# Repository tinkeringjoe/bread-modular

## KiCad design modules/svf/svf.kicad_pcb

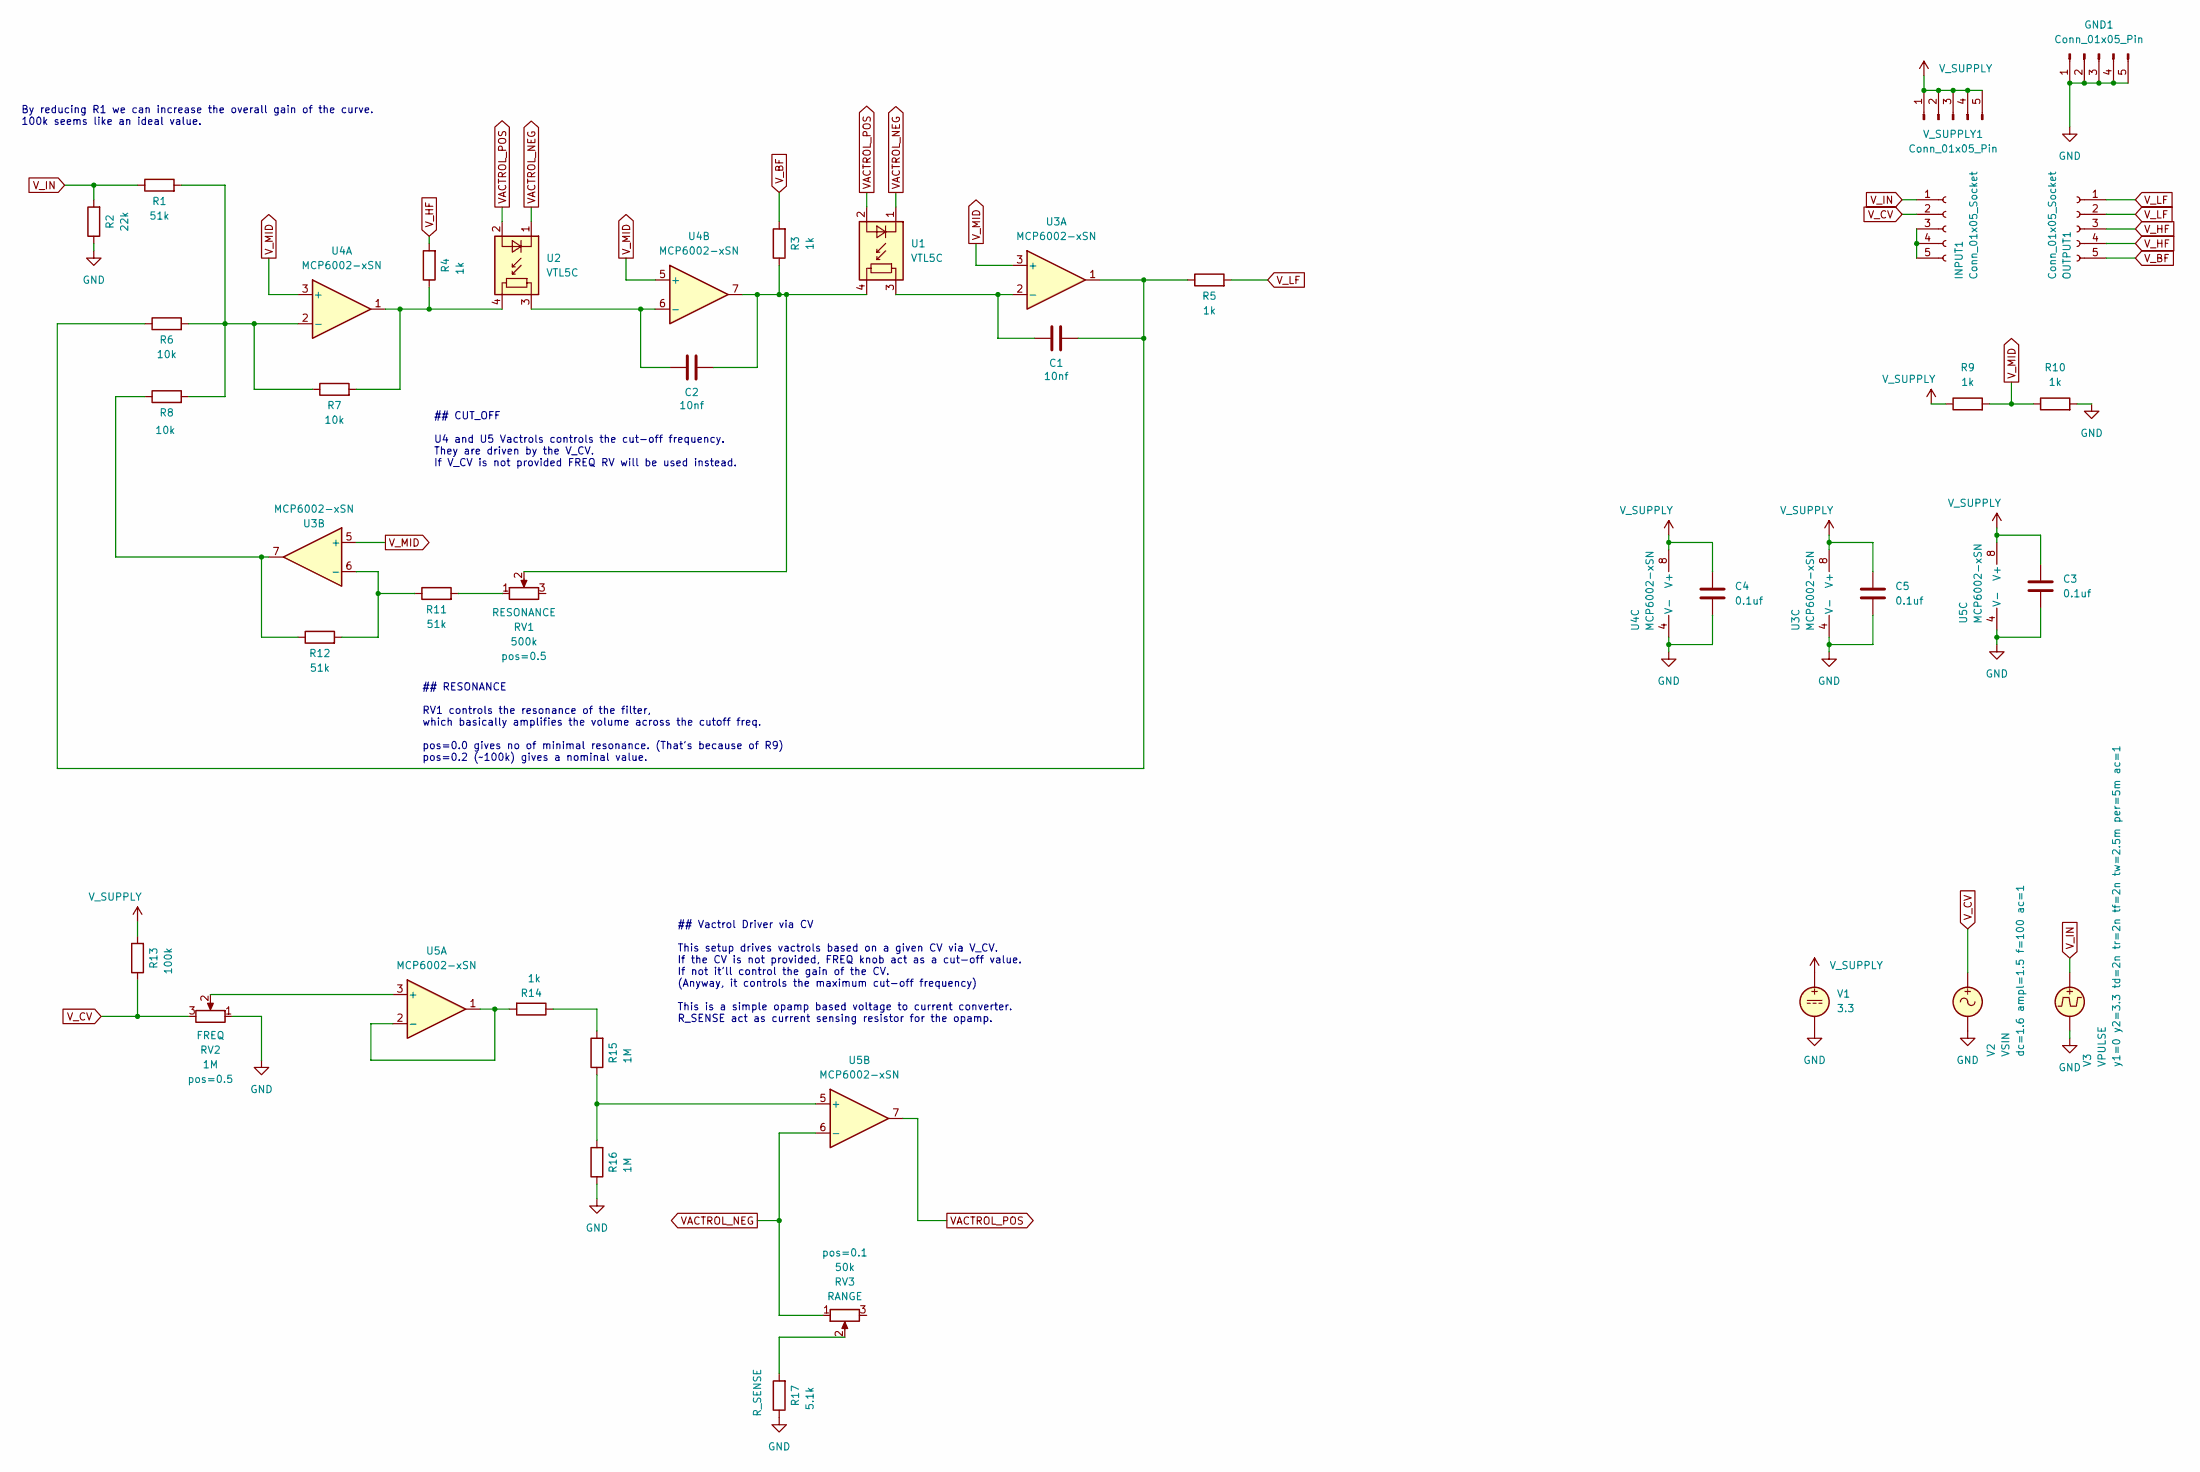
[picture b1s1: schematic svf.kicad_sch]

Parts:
C1, C2: 10nf; C_0402_1005Metric
C3, C4, C5: 0.1uf; C_0402_1005Metric
GND1: Conn_01x05_Pin; Power_Connector
INPUT1: Conn_01x05_Socket; PinSocket_1x05_P2.54mm_Vertical
OUTPUT1: Conn_01x05_Socket; PinSocket_1x05_P2.54mm_Vertical
R1, R11, R12: 51k; R_0402_1005Metric
R2: 22k; R_0402_1005Metric
R3, R4, R5, R9, R10, R14: 1k; R_0402_1005Metric
R6, R7, R8: 10k; R_0402_1005Metric
R13: 100k; R_0402_1005Metric
R15, R16: 1M; R_0402_1005Metric
R17: 5.1k; R_0402_1005Metric
RV1: 500k; Potentiometer_RV09
RV2: 1M; Potentiometer_RV09
RV3: 50k; Potentiometer_RV09
U1, U2: VTL5C
U3, U4, U5: MCP6002-xSN; SOIC-8-1EP_3.9x4.9mm_P1.27mm_EP2.29x3mm
V1: 3.3
V2: VSIN
V3: VPULSE
V_SUPPLY1: Conn_01x05_Pin; Power_Connector

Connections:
GND: C3.2, C4.2, C5.2, GND1.1, GND1.2, GND1.3, GND1.4, GND1.5, R2.1, R10.2, R16.1, R17.1, RV2.1, U3.4 (V-), U4.4 (V-), U5.4 (V-), V1.2, V2.2, V3.2
unnamed: C1.2, R5.1, R6.1, U3.1
unnamed: C2.2, R3.1, RV1.2, U1.4, U4.7
unnamed: INPUT1.3, INPUT1.4, INPUT1.5
unnamed: R4.1, R7.2, U2.4, U4.1
unnamed: R11.2, RV1.1
unnamed: R8.1, R12.1, U3.7
unnamed: R14.1, R15.2
unnamed: R17.2, RV3.2
unnamed: C1.1, U1.3, U3.2 (-)
unnamed: R11.1, R12.2, U3.6 (-)
unnamed: R1.2, R6.2, R7.1, R8.2, U4.2 (-)
unnamed: C2.1, U2.3, U4.6 (-)
unnamed: RV2.2, U5.3 (+)
unnamed: R14.2, U5.1, U5.2 (-)
unnamed: R15.1, R16.2, U5.5 (+)
VACTROL_NEG: RV3.1, U1.1 (-), U2.1 (-), U5.6 (-)
VACTROL_POS: U1.2 (+), U2.2 (+), U5.7
V_BF: OUTPUT1.5, R3.2
V_CV: INPUT1.2, R13.1, RV2.3, V2.1
V_HF: OUTPUT1.3, OUTPUT1.4, R4.2
V_IN: INPUT1.1, R1.1, R2.2, V3.1
V_LF: OUTPUT1.1, OUTPUT1.2, R5.2
V_MID: R9.2, R10.1, U3.3 (+), U3.5 (+), U4.3 (+), U4.5 (+)
V_SUPPLY: C3.1, C4.1, C5.1, R9.1, R13.2, U3.8 (V+), U4.8 (V+), U5.8 (V+), V1.1, V_SUPPLY1.1, V_SUPPLY1.2, V_SUPPLY1.3, V_SUPPLY1.4, V_SUPPLY1.5

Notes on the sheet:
## Vactrol Driver via CV This setup drives vactrols based on a given CV via V_CV. If the CV is not provided, FREQ knob act as a cut-off value. If not it'll control the gain of the CV. (Anyway, it controls the maximum cut-off frequency) This is a simple opamp based voltage to current converter. R_SE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
## CUT_OFF U4 and U5 Vactrols controls the cut-off frequency. They are driven by the V_CV. If V_CV is not provided FREQ RV will be used instead.
## RESONANCE RV1 controls the resonance of the filter, which basically amplifies the volume across the cutoff freq. pos=0.0 gives no of minimal resonance. (That's because of R9) pos=0.2 (~100k) gives a nominal value.
By reducing R1 we can increase the overall gain of the curve. 100k seems like an ideal value.

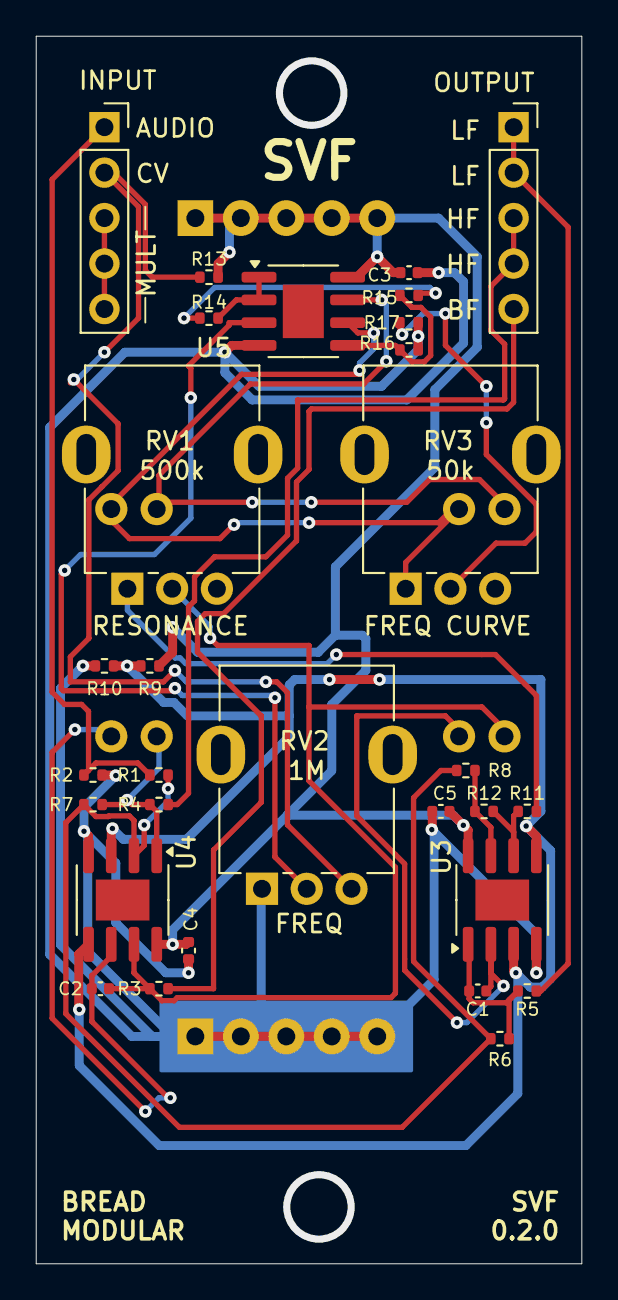
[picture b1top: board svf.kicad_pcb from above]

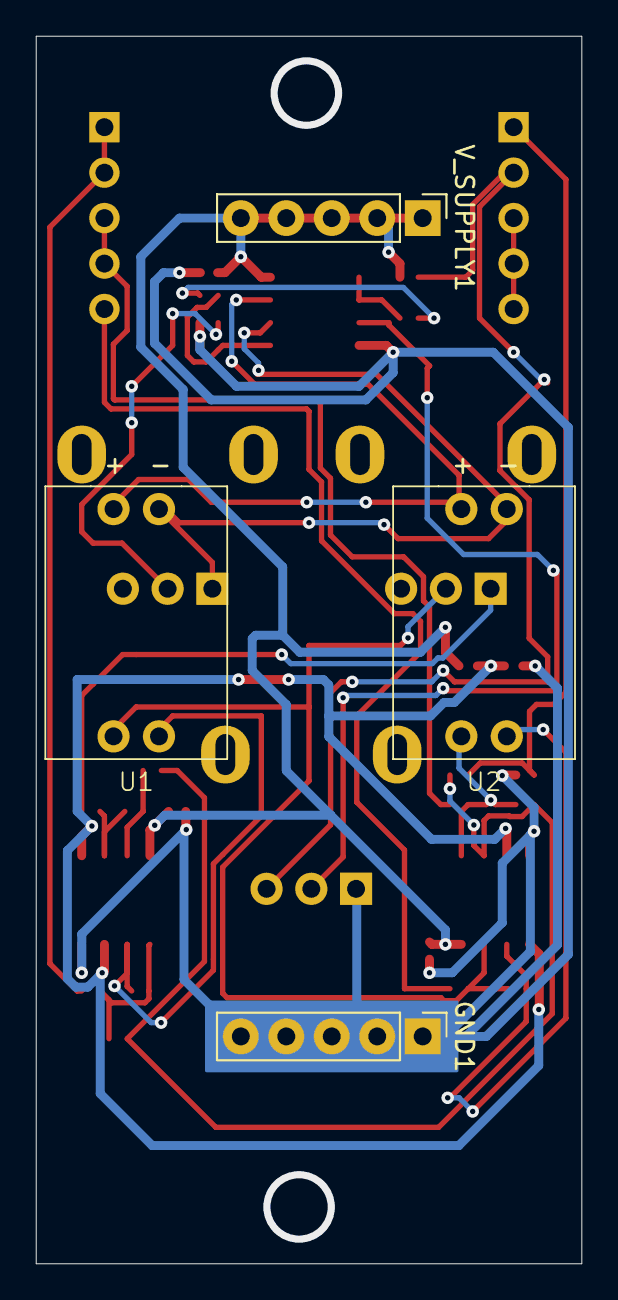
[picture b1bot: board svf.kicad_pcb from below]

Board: 2 copper layers, 30.5 x 68.6 mm, 34 parts (4 on the bottom side), 25 nets.

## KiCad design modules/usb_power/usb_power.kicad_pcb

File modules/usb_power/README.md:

# USB_Power

A simple power source from USB.

## Usage

This plug a USB-C and now we have power to the system.<br/>
This makes is not only to get power from computer, but using bunch of power source including your phone. This will be the only power source we'll ever need.

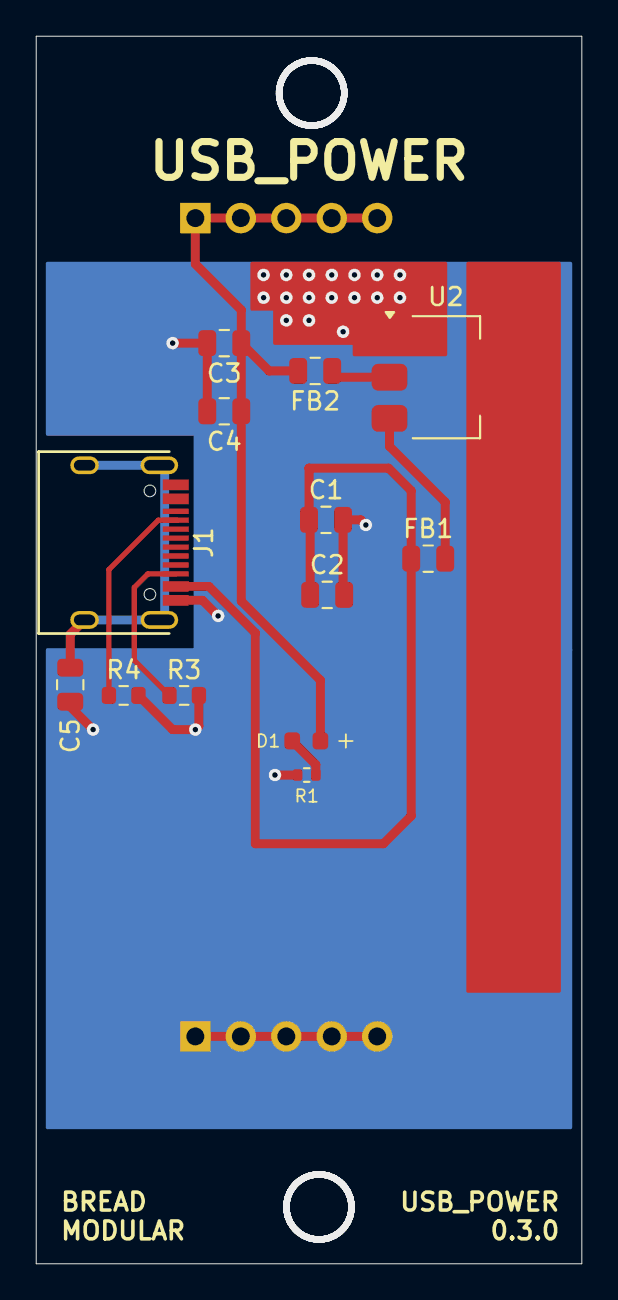
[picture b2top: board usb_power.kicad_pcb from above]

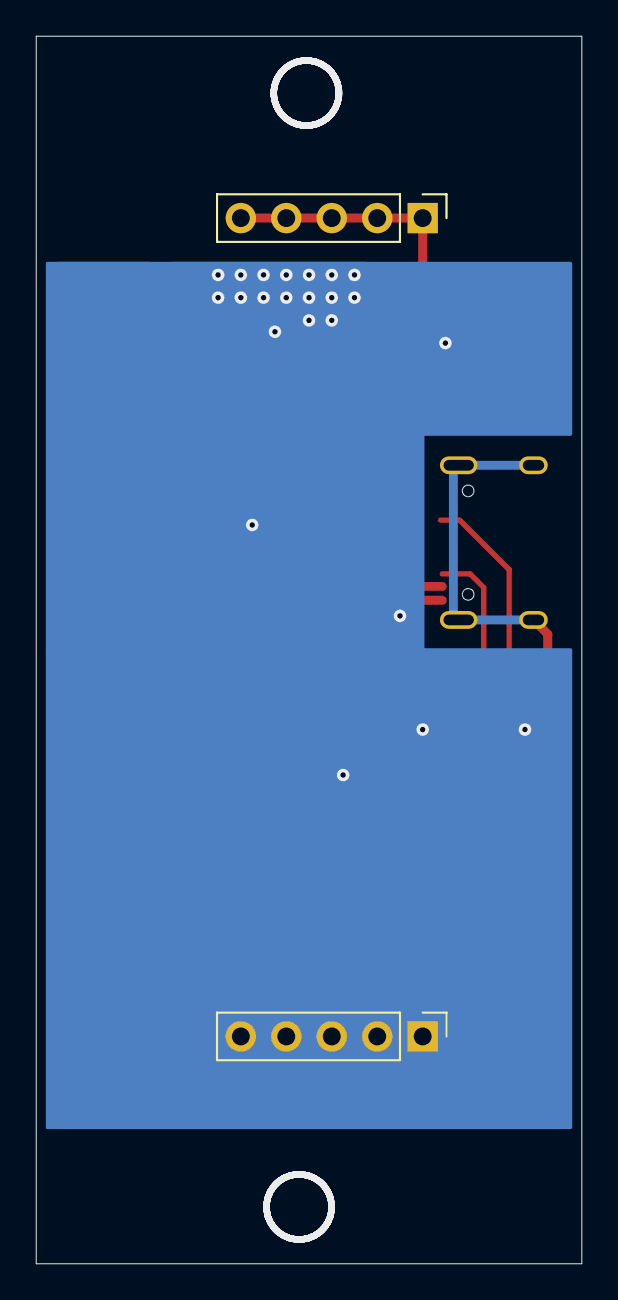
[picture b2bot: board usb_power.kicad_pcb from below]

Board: 2 copper layers, 30.5 x 68.6 mm, 15 parts (2 on the bottom side), 9 nets.

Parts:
5V1: Conn_01x05_Pin; PinHeader_1x05_P2.54mm_Vertical
C1, C3: 10uf; C_0805_2012Metric
C2, C4: 0.1uf; C_0805_2012Metric
C5: 10nf; C_0805_2012Metric
D1: LED; LED_0603_1608Metric
FB1, FB2: GZ2012E800TF; C_0805_2012Metric
GND1: Conn_01x05_Pin; PinHeader_1x05_P2.54mm_Vertical
J1: USB_C_Receptacle_PowerOnly_6P; HRO-TYPE-C-31-M-12
R1: 1k; R_0402_1005Metric
R3, R4: 5.1k; R_0603_1608Metric
U2: AMS1117-3.3; SOT-223

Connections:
+3.3V: 5V1.1, 5V1.2, 5V1.3, 5V1.4, 5V1.5, C3.1, C4.1, D1.2 (A), FB2.2
GND: C1.2, C2.2, C3.2, C4.2, C5.2, GND1.1, GND1.2, GND1.3, GND1.4, GND1.5, J1.A12 (GND), R1.2, R3.2, R4.2, U2.1 (GND)
unnamed: C1.1, C2.1, FB1.1, J1.A9 (VBUS)
unnamed: D1.1 (K), R1.1
unnamed: J1.A5 (CC1), R4.1
unnamed: J1.B5 (CC2), R3.1
unnamed: C5.1, J1.S1 (SHIELD)
unnamed: FB1.2, U2.3 (VI)
unnamed: FB2.1, U2.2 (VO)

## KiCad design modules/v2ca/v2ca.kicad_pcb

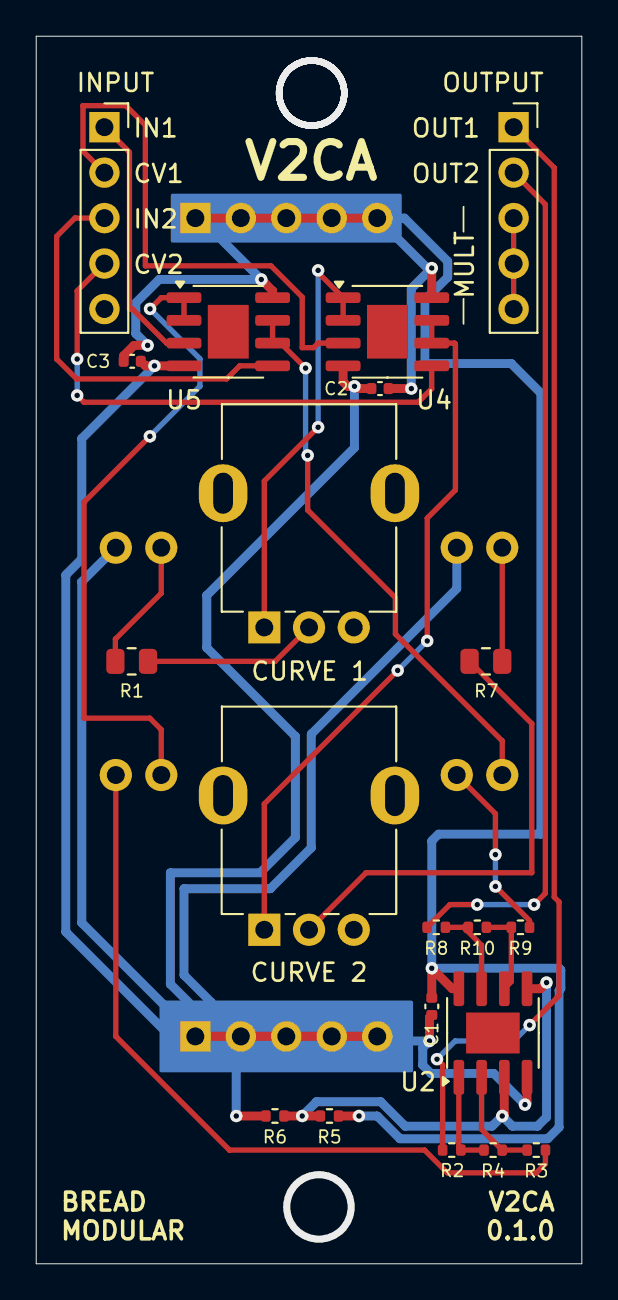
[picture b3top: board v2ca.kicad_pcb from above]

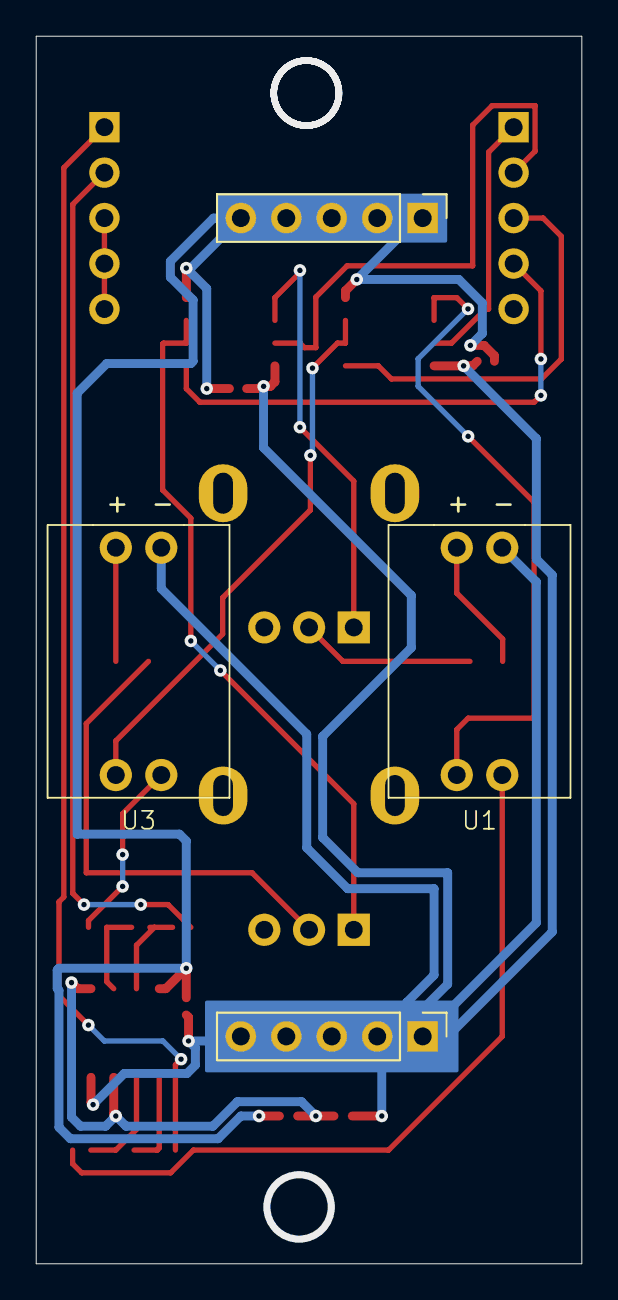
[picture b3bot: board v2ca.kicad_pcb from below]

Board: 2 copper layers, 30.5 x 68.6 mm, 24 parts (4 on the bottom side), 24 nets.

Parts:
5V1: Conn_01x05_Pin; PinHeader_1x05_P2.54mm_Vertical
C1, C2, C3: 0.1uf; C_0402_1005Metric
GND1: Conn_01x05_Pin; PinHeader_1x05_P2.54mm_Vertical
INPUT1: Conn_01x05_Socket; PinSocket_1x05_P2.54mm_Vertical
OUTPUT1: Conn_01x05_Socket; PinSocket_1x05_P2.54mm_Vertical
R1, R7: 330; R_0805_2012Metric
R2, R5, R6, R8: 1k; R_0402_1005Metric
R3, R4, R9, R10: 10k; R_0402_1005Metric
RV1, RV2: 50k; Potentiometer_RV09
U1, U3: VTL5C
U2, U4, U5: MCP6002-xSN; SOIC-8-1EP_3.9x4.9mm_P1.27mm_EP2.29x3mm

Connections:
+2.5V: R5.2, R6.1, U2.3 (+), U2.5 (+)
+5V: 5V1.1, 5V1.2, 5V1.3, 5V1.4, 5V1.5, C1.1, C2.1, C3.1, R5.1, U2.8 (V+), U4.8 (V+), U5.8 (V+)
CV1_IN: INPUT1.2, U4.3 (+)
CV2_IN: INPUT1.4, U4.5 (+)
GND: C1.2, C2.2, C3.2, GND1.1, GND1.2, GND1.3, GND1.4, GND1.5, R6.2, U1.1 (-), U2.4 (V-), U3.1 (-), U4.4 (V-), U5.4 (V-)
unnamed: OUTPUT1.3, OUTPUT1.4, OUTPUT1.5
unnamed: R1.1, RV1.2
unnamed: R2.1, R4.2, U2.1
unnamed: R3.1, U1.3
unnamed: R7.1, RV2.2
unnamed: R9.1, U3.3
unnamed: R8.1, R10.2, U2.7
unnamed: R1.2, U1.2 (+)
unnamed: R3.2, R4.1, U2.2 (-)
unnamed: R9.2, R10.1, U2.6 (-)
unnamed: R7.2, U3.2 (+)
unnamed: RV1.1, U4.1, U4.2 (-)
unnamed: RV2.1, U4.6 (-), U4.7
unnamed: U1.4, U5.1, U5.2 (-)
unnamed: U3.4, U5.6 (-), U5.7
V1_IN: INPUT1.1, U5.3 (+)
V1_OUT: OUTPUT1.1, R2.2
V2_IN: INPUT1.3, U5.5 (+)
V2_OUT: OUTPUT1.2, R8.2

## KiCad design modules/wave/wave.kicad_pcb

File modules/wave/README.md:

# Wave

A Simple Waveform generator based on opamp relaxation oscillators. It can generate:

* Square
* Triangle 
* Sine (only upword 45Hz)

## Configurations

Before we use this module, we need to configure and select the frequence range via the config jumping panel.

Here are the frequency ranges:

* LFO - 0.22Hz to 22Hz
* LOW - 15Hz to 1.5kHz
* HIGH - 227Hz to 22kHz
* C1 & C2 - Add custom capacitors
  (Resistance => Min: 10k, Max: 1M)

## Usage

You can select the frequency using "FREQ" potentiometer which is 1M ohms. Then you can fine tune it via the 50k ohms "FINE" potentiometer.

(Turning clockwise reduces the resistance)

## Notes

* Does not produce any results, when it's not configured
* Triangle waveform is appoximated & it's not a pure triangle
* Sine wave got distroted when the frequncy is below 45Hz
* Sine wave will be attenuated as the freq increases
* No voltage control input or modulation is supported

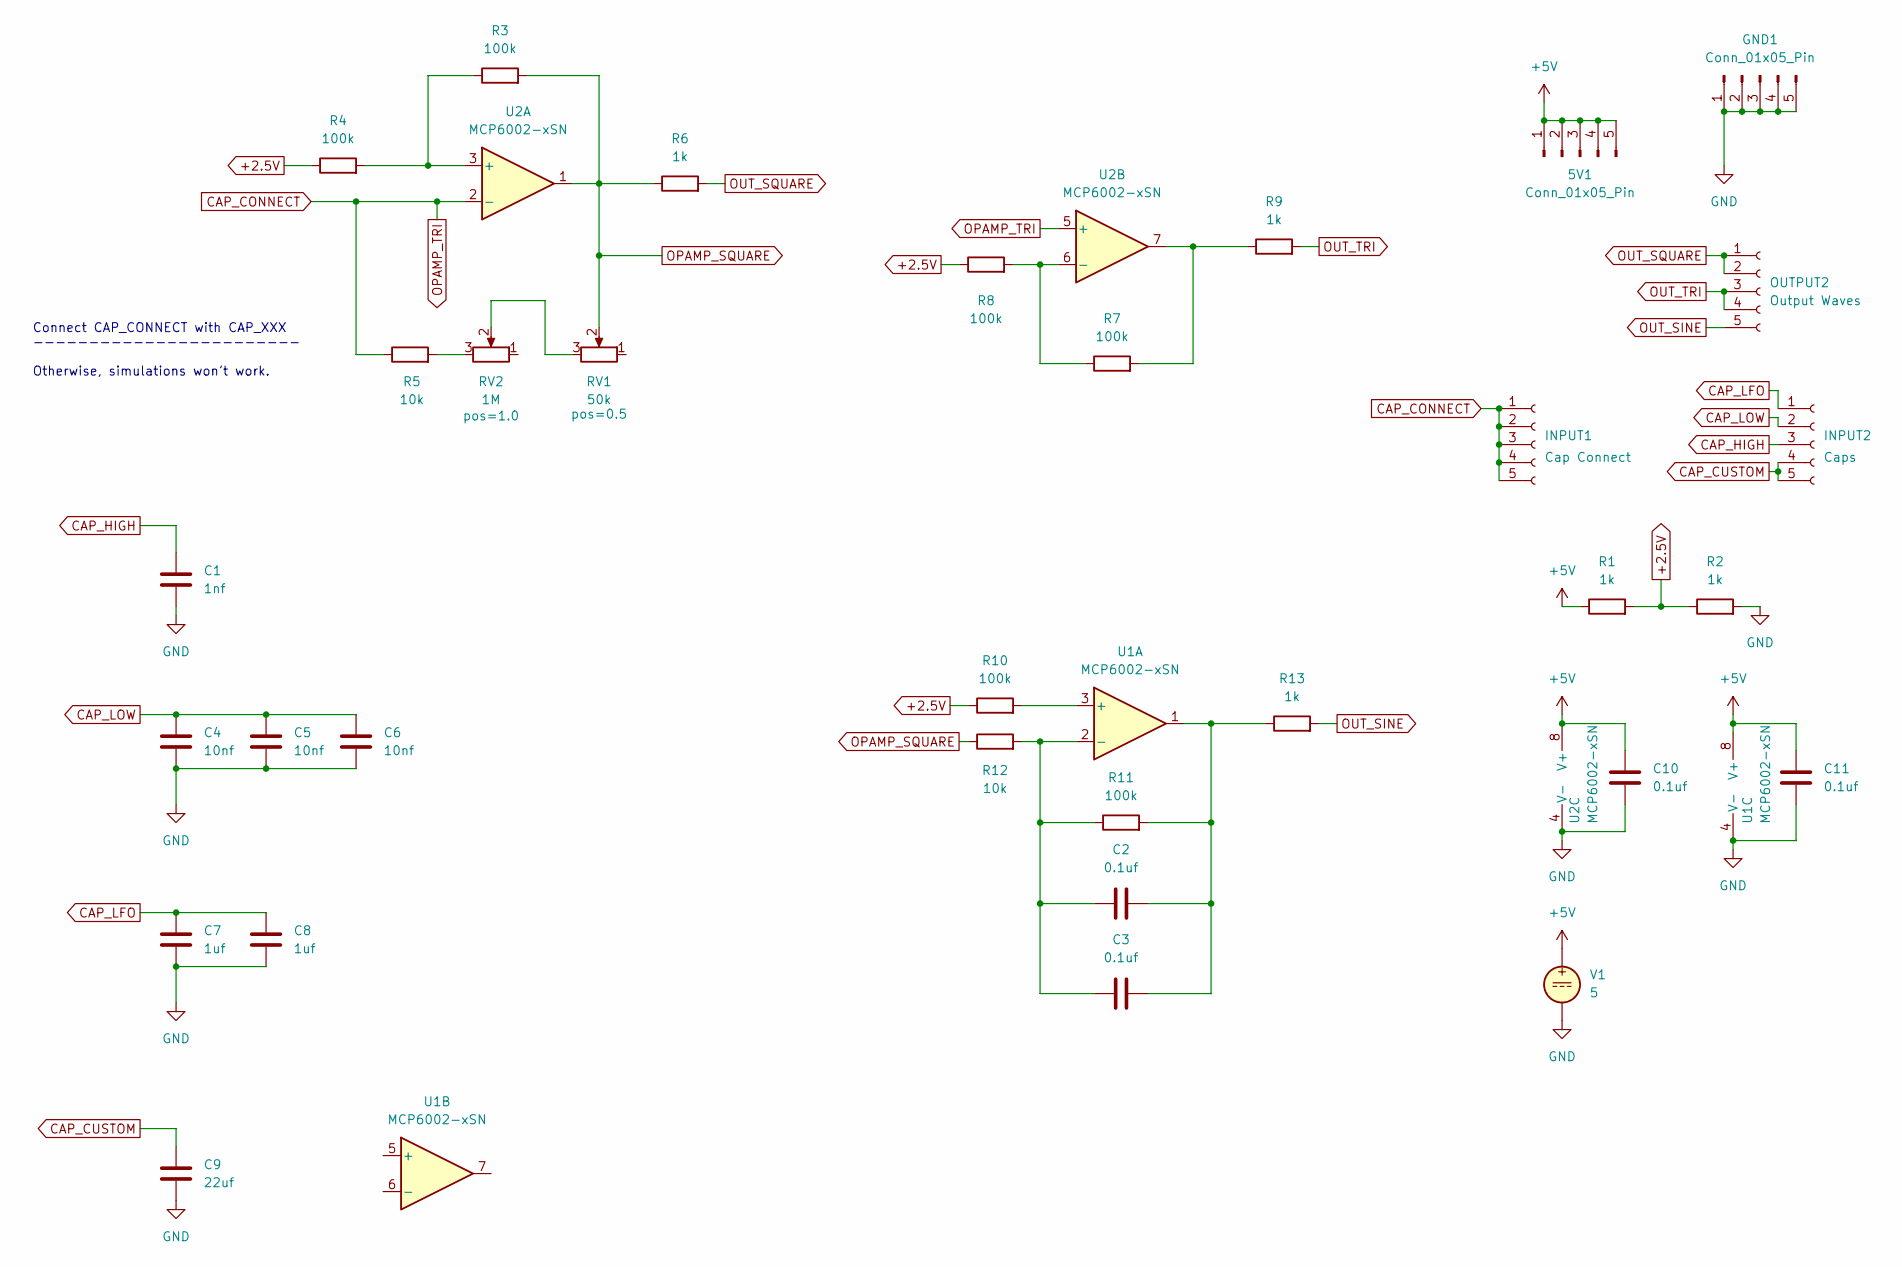
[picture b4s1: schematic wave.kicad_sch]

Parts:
5V1: Conn_01x05_Pin; PinHeader_1x05_P2.54mm_Vertical
C1: 1nf; C_0402_1005Metric
C2, C3, C10, C11: 0.1uf; C_0402_1005Metric
C4, C5, C6: 10nf; C_0402_1005Metric
C7, C8: 1uf; C_0402_1005Metric
C9: 22uf; C_0805_2012Metric
GND1: Conn_01x05_Pin; PinHeader_1x05_P2.54mm_Vertical
INPUT1: Cap Connect; PinSocket_1x05_P2.54mm_Vertical
INPUT2: Caps; PinSocket_1x05_P2.54mm_Vertical
OUTPUT2: Output Waves; PinSocket_1x05_P2.54mm_Vertical
R1, R2, R6, R9, R13: 1k; R_0402_1005Metric
R3, R4, R7, R8, R10, R11: 100k; R_0402_1005Metric
R5, R12: 10k; R_0402_1005Metric
RV1: 50k; Potentiometer_RV09
RV2: 1M; Potentiometer_RV09
U1, U2: MCP6002-xSN; SOIC-8-1EP_3.9x4.9mm_P1.27mm_EP2.29x3mm
V1: 5

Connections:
+2.5V: R1.2, R2.1, R4.1, R8.1, R10.1
+5V: 5V1.1, 5V1.2, 5V1.3, 5V1.4, 5V1.5, C10.1, C11.1, R1.1, U1.8 (V+), U2.8 (V+), V1.1
CAP_CONNECT: INPUT1.1, INPUT1.2, INPUT1.3, INPUT1.4, INPUT1.5, R5.1, U2.2 (-), U2.5 (+)
CAP_CUSTOM: C9.1, INPUT2.4, INPUT2.5
CAP_HIGH: C1.1, INPUT2.3
CAP_LFO: C7.1, C8.1, INPUT2.1
CAP_LOW: C4.1, C5.1, C6.1, INPUT2.2
GND: C1.2, C4.2, C5.2, C6.2, C7.2, C8.2, C9.2, C10.2, C11.2, GND1.1, GND1.2, GND1.3, GND1.4, GND1.5, R2.2, U1.4 (V-), U2.4 (V-), V1.2
unnamed: C2.2, C3.2, R11.2, R13.1, U1.1
unnamed: R5.2, RV2.3
unnamed: R7.2, R9.1, U2.7
unnamed: RV1.3, RV2.2
unnamed: R10.2, U1.3 (+)
unnamed: C2.1, C3.1, R11.1, R12.2, U1.2 (-)
unnamed: R3.1, R4.2, U2.3 (+)
unnamed: R7.1, R8.2, U2.6 (-)
OPAMP_SQUARE: R3.2, R6.1, R12.1, RV1.2, U2.1
OUT_SINE: OUTPUT2.5, R13.2
OUT_SQUARE: OUTPUT2.1, OUTPUT2.2, R6.2
OUT_TRI: OUTPUT2.3, OUTPUT2.4, R9.2

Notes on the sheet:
Connect CAP_CONNECT with CAP_XXX ------------------------ Otherwise, simulations won't work.

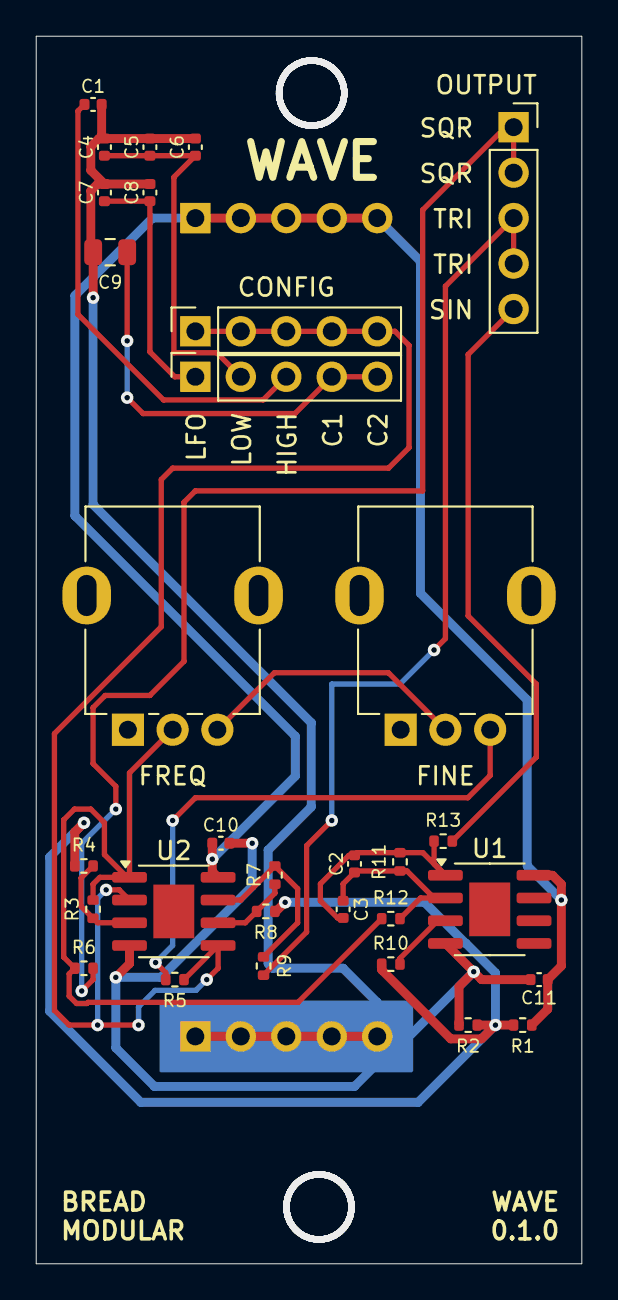
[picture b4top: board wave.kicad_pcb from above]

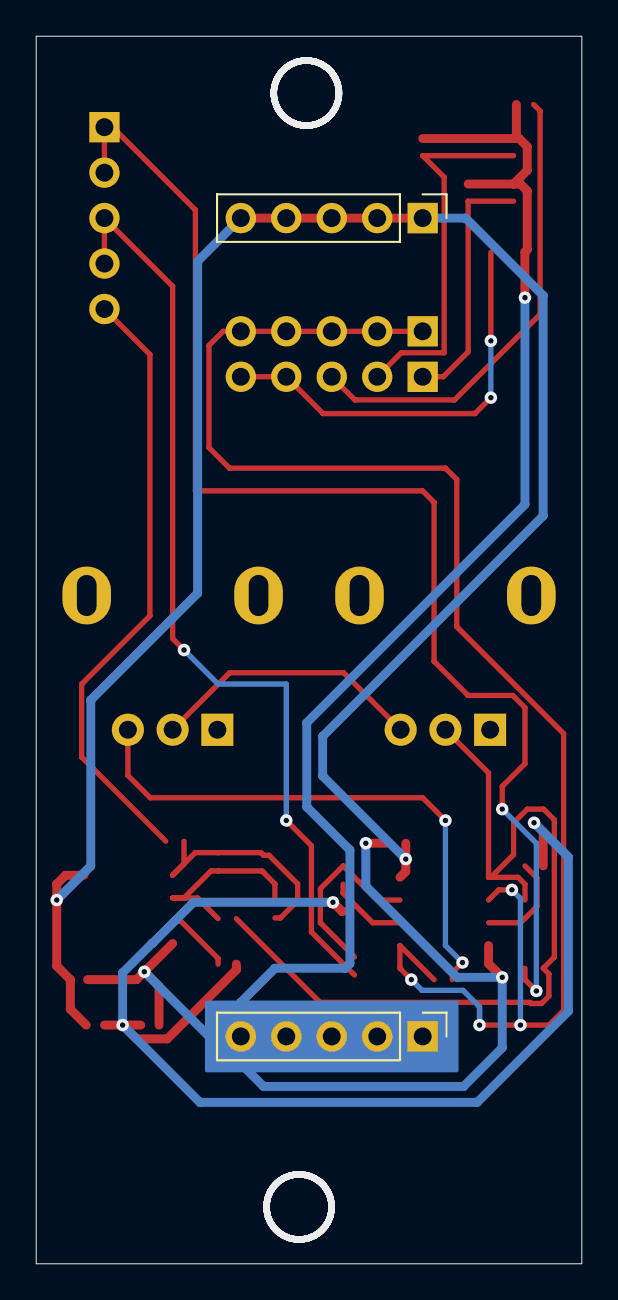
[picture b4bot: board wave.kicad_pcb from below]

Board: 2 copper layers, 30.5 x 68.6 mm, 33 parts (2 on the bottom side), 20 nets.

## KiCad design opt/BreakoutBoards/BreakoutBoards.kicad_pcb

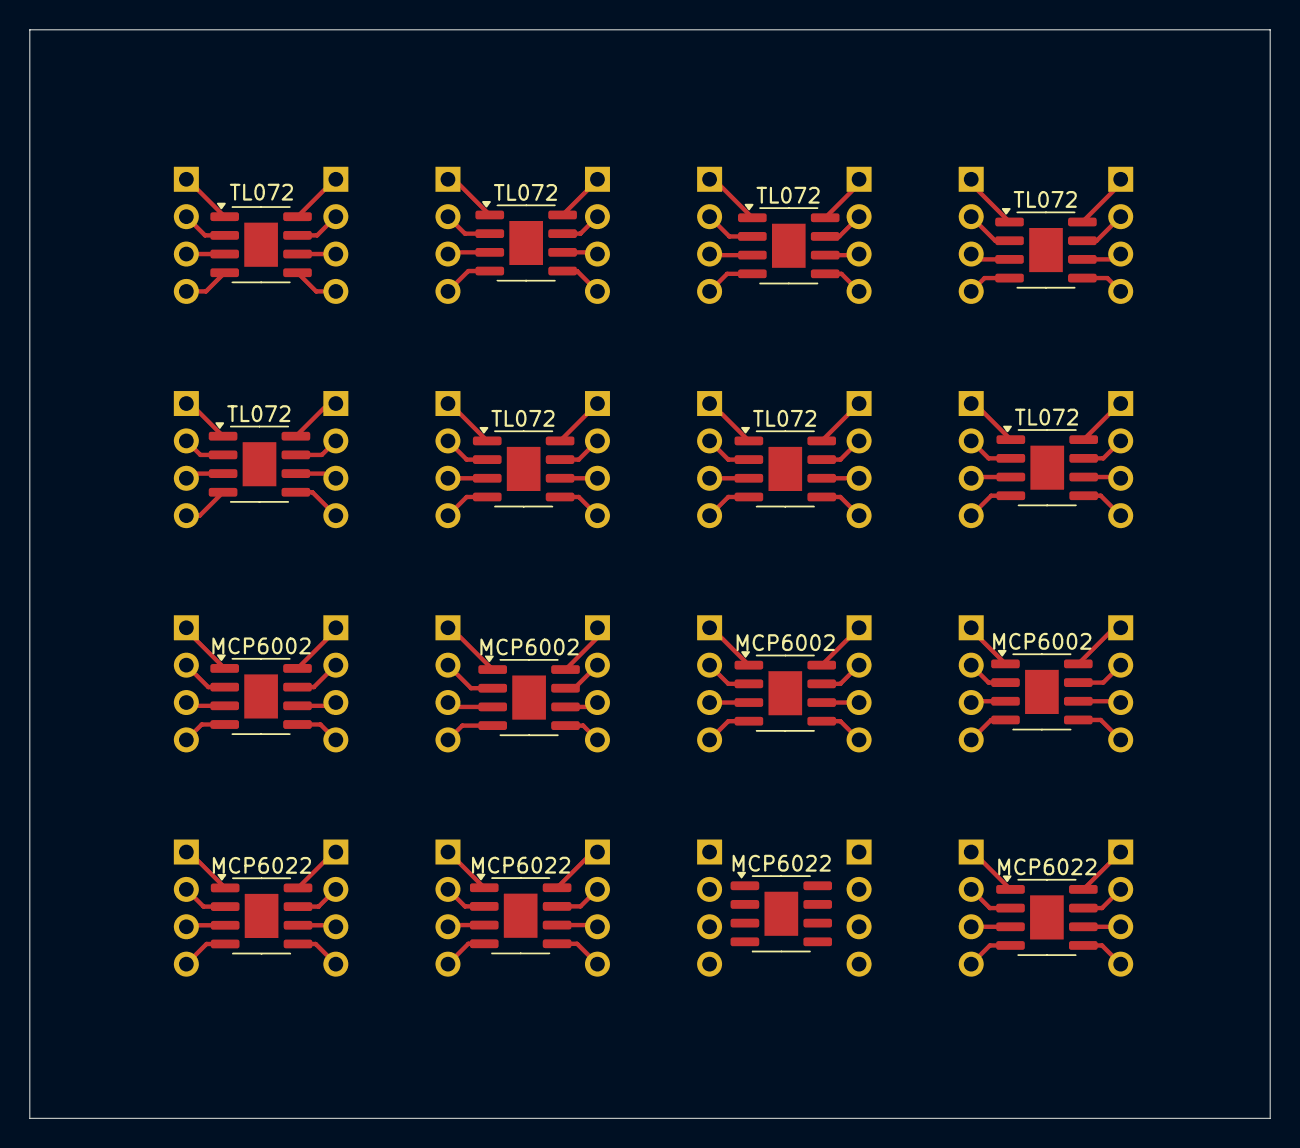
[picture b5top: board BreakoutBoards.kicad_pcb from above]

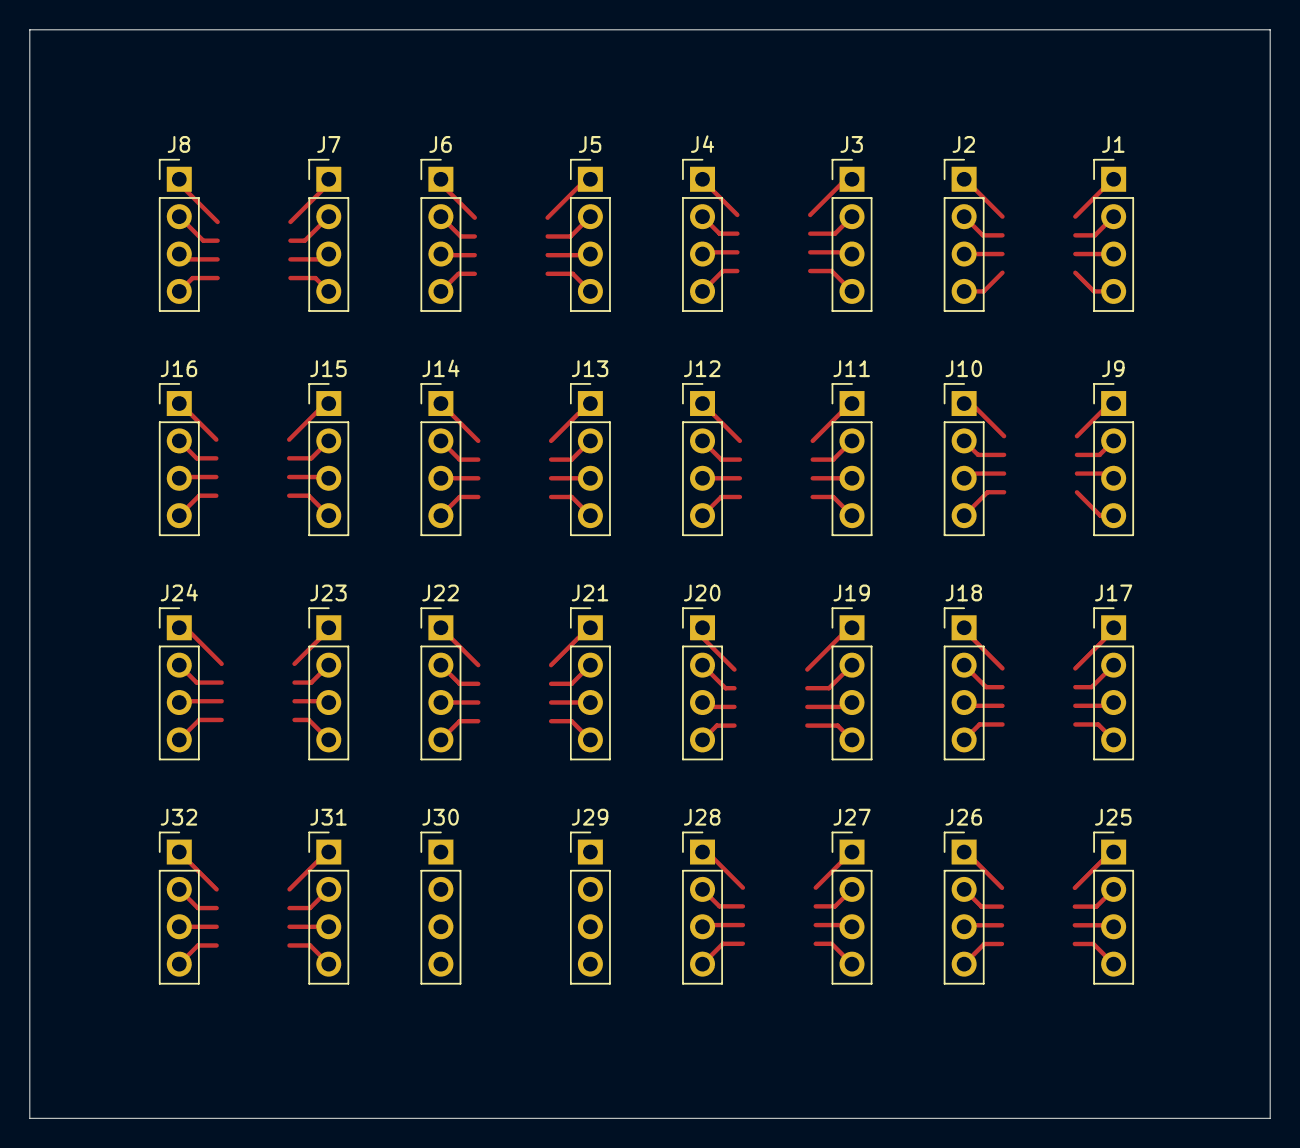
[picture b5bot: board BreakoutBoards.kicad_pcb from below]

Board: 2 copper layers, 84.3 x 74.0 mm, 48 parts (32 on the bottom side), 128 nets.

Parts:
J1, J2, J3, J4, J5, J6, J7, J8, J9, J10, J11, J12, J13, J14, J15, J16, J17, J18, J19, J20, J21, J22, J23, J24, J25, J26, J27, J28, J29, J30, J31, J32: Conn_01x04_Pin; PinHeader_1x04_P2.54mm_Vertical
MCP6002, MCP6002#2, MCP6002#3, MCP6002#4: MCP6002-xSN; SOIC-8-1EP_3.9x4.9mm_P1.27mm_EP2.29x3mm
MCP6022, MCP6022#2, MCP6022#3, MCP6022#4: MCP6022; SOIC-8-1EP_3.9x4.9mm_P1.27mm_EP2.29x3mm
TL072, TL072#2, TL072#3, TL072#4, TL072#5, TL072#6, TL072#7, TL072#8: TL072; SOIC-8-1EP_3.9x4.9mm_P1.27mm_EP2.29x3mm

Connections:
unnamed: J1.1, TL072.1
unnamed: J1.2, TL072.2 (-)
unnamed: J1.3, TL072.3 (+)
unnamed: J1.4, TL072.4 (V-)
unnamed: J2.1, TL072.8 (V+)
unnamed: J2.2, TL072.7
unnamed: J2.3, TL072.6 (-)
unnamed: J2.4, TL072.5 (+)
unnamed: J3.1, TL072#2.1
unnamed: J3.2, TL072#2.2 (-)
unnamed: J3.3, TL072#2.3 (+)
unnamed: J3.4, TL072#2.4 (V-)
unnamed: J4.1, TL072#2.8 (V+)
unnamed: J4.2, TL072#2.7
unnamed: J4.3, TL072#2.6 (-)
unnamed: J4.4, TL072#2.5 (+)
unnamed: J5.1, TL072#6.1
unnamed: J5.2, TL072#6.2 (-)
unnamed: J5.3, TL072#6.3 (+)
unnamed: J5.4, TL072#6.4 (V-)
unnamed: J6.1, TL072#6.8 (V+)
unnamed: J6.2, TL072#6.7
unnamed: J6.3, TL072#6.6 (-)
unnamed: J6.4, TL072#6.5 (+)
unnamed: J7.1, TL072#3.1
unnamed: J7.2, TL072#3.2 (-)
unnamed: J7.3, TL072#3.3 (+)
unnamed: J7.4, TL072#3.4 (V-)
unnamed: J8.1, TL072#3.8 (V+)
unnamed: J8.2, TL072#3.7
unnamed: J8.3, TL072#3.6 (-)
unnamed: J8.4, TL072#3.5 (+)
unnamed: J9.1, TL072#8.1
unnamed: J9.2, TL072#8.2 (-)
unnamed: J9.3, TL072#8.3 (+)
unnamed: J9.4, TL072#8.4 (V-)
unnamed: J10.1, TL072#8.8 (V+)
unnamed: J10.2, TL072#8.7
unnamed: J10.3, TL072#8.6 (-)
unnamed: J10.4, TL072#8.5 (+)
unnamed: J11.1, TL072#4.1
unnamed: J11.2, TL072#4.2 (-)
unnamed: J11.3, TL072#4.3 (+)
unnamed: J11.4, TL072#4.4 (V-)
unnamed: J12.1, TL072#4.8 (V+)
unnamed: J12.2, TL072#4.7
unnamed: J12.3, TL072#4.6 (-)
unnamed: J12.4, TL072#4.5 (+)
unnamed: J13.1, TL072#7.1
unnamed: J13.2, TL072#7.2 (-)
unnamed: J13.3, TL072#7.3 (+)
unnamed: J13.4, TL072#7.4 (V-)
unnamed: J14.1, TL072#7.8 (V+)
unnamed: J14.2, TL072#7.7
unnamed: J14.3, TL072#7.6 (-)
unnamed: J14.4, TL072#7.5 (+)
unnamed: J15.1, TL072#5.1
unnamed: J15.2, TL072#5.2 (-)
unnamed: J15.3, TL072#5.3 (+)
unnamed: J15.4, TL072#5.4 (V-)
unnamed: J16.1, TL072#5.8 (V+)
unnamed: J16.2, TL072#5.7
unnamed: J16.3, TL072#5.6 (-)
unnamed: J16.4, TL072#5.5 (+)
unnamed: J17.1, MCP6002#3.1
unnamed: J17.2, MCP6002#3.2 (-)
unnamed: J17.3, MCP6002#3.3 (+)
unnamed: J17.4, MCP6002#3.4 (V-)
unnamed: J18.1, MCP6002#3.8 (V+)
unnamed: J18.2, MCP6002#3.7
unnamed: J18.3, MCP6002#3.6 (-)
unnamed: J18.4, MCP6002#3.5 (+)
unnamed: J19.1, MCP6002#2.1
unnamed: J19.2, MCP6002#2.2 (-)
unnamed: J19.3, MCP6002#2.3 (+)
unnamed: J19.4, MCP6002#2.4 (V-)
unnamed: J20.1, MCP6002#2.8 (V+)
unnamed: J20.2, MCP6002#2.7
unnamed: J20.3, MCP6002#2.6 (-)
unnamed: J20.4, MCP6002#2.5 (+)
unnamed: J21.1, MCP6002.1
unnamed: J21.2, MCP6002.2 (-)
unnamed: J21.3, MCP6002.3 (+)
unnamed: J21.4, MCP6002.4 (V-)
unnamed: J22.1, MCP6002.8 (V+)
unnamed: J22.2, MCP6002.7
unnamed: J22.3, MCP6002.6 (-)
unnamed: J22.4, MCP6002.5 (+)
unnamed: J23.1, MCP6002#4.1
unnamed: J23.2, MCP6002#4.2 (-)
unnamed: J23.3, MCP6002#4.3 (+)
unnamed: J23.4, MCP6002#4.4 (V-)
unnamed: J24.1, MCP6002#4.8 (V+)
unnamed: J24.2, MCP6002#4.7
unnamed: J24.3, MCP6002#4.6 (-)
unnamed: J24.4, MCP6002#4.5 (+)
unnamed: J25.1, MCP6022#3.1
unnamed: J25.2, MCP6022#3.2 (-)
unnamed: J25.3, MCP6022#3.3 (+)
unnamed: J25.4, MCP6022#3.4 (V-)
unnamed: J26.1, MCP6022#3.8 (V+)
unnamed: J26.2, MCP6022#3.7
unnamed: J26.3, MCP6022#3.6 (-)
unnamed: J26.4, MCP6022#3.5 (+)
unnamed: J27.1, MCP6022.1
unnamed: J27.2, MCP6022.2 (-)
unnamed: J27.3, MCP6022.3 (+)
unnamed: J27.4, MCP6022.4 (V-)
unnamed: J28.1, MCP6022.8 (V+)
unnamed: J28.2, MCP6022.7
unnamed: J28.3, MCP6022.6 (-)
unnamed: J28.4, MCP6022.5 (+)
unnamed: J29.1, MCP6022#2.1
unnamed: J29.2, MCP6022#2.2 (-)
unnamed: J29.3, MCP6022#2.3 (+)
unnamed: J29.4, MCP6022#2.4 (V-)
unnamed: J30.1, MCP6022#2.8 (V+)
unnamed: J30.2, MCP6022#2.7
unnamed: J30.3, MCP6022#2.6 (-)
unnamed: J30.4, MCP6022#2.5 (+)
unnamed: J31.1, MCP6022#4.1
unnamed: J31.2, MCP6022#4.2 (-)
unnamed: J31.3, MCP6022#4.3 (+)
unnamed: J31.4, MCP6022#4.4 (V-)
unnamed: J32.1, MCP6022#4.8 (V+)
unnamed: J32.2, MCP6022#4.7
unnamed: J32.3, MCP6022#4.6 (-)
unnamed: J32.4, MCP6022#4.5 (+)
